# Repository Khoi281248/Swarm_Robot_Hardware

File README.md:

# Swarm Robot – Hardware

Mạch điều khiển cho robot bầy đàn (swarm robot), thiết kế bằng **KiCad 10**.

Một mạch duy nhất gồm hai vi điều khiển:
- **STM32F103C8T6**: điều khiển thời gian thực. Lo 2 động cơ có encoder, IMU 6 trục và đo điện áp pin.
- **ESP32-C3-WROOM-02**: truyền thông không dây giữa các robot. Chip này cũng nạp firmware cho STM32 qua UART.

> 🔗 Firmware: [Swarm_Robot_Firmware](https://github.com/Khoi281248/Swarm_Robot_Firmware)
> 📄 Sơ đồ nguyên lý dạng PDF (xem không cần KiCad): [Swarm_robot_project.pdf](Swarm_robot_project.pdf)

| Mặt trên (3D) | Mặt dưới (3D) |
|---|---|
|  |  |

*Ảnh render 3D từ KiCad 10. Linh kiện xuyên lỗ J1–J4, SW3, SW5 là DNP (tự hàn) nên không hiện model 3D.*

<details>
<summary>Đi dây lớp đồng (bấm để xem)</summary>

| Lớp trên F.Cu | Lớp dưới B.Cu (nhìn từ dưới) |
|---|---|
|  |  |

</details>

## Thông số mạch

| Thông số | Giá trị |
|---|---|
| Kích thước | 62,8 × 62,8 mm, hình bát giác |
| Số lớp | 2 lớp (F.Cu tín hiệu, B.Cu nguồn/GND), dày 1,6 mm |
| Lỗ bắt vít | 4 lỗ M2 (H1–H4) |
| Nguồn | Pin LiPo 1S (2000 mAh), sạc qua USB-C |
| Linh kiện | 87 footprint: 77 linh kiện SMD lắp tại JLCPCB, 6 linh kiện xuyên lỗ tự hàn (J1–J4, SW3, SW5), 4 lỗ vít |

## Sơ đồ khối

```
 USB-C (J5) ──┬── D+/D- ── USBLC6 (U7) ──────────────► ESP32-C3 (USB Serial/JTAG)
              │
              └── VBUS ──► BQ24075 (U3) ◄──► Pin LiPo 1S (J4)
                           sạc + power-path
                                │ VOUT   (SW5: bật/tắt nguồn)
                  ┌─────────────┴──────────────┐
                  ▼                            ▼
          TPS63802 (U1)                 MT3608 (U2) + SS34 (D1)
          buck-boost → +3,3 V           boost → +6 V
                  │                            │
   STM32, ESP32-C3, IMU, encoder         DRV8833 (U4) ──► Motor A (J1), Motor B (J2)

   ESP32-C3 ── UART (TX_ESP / RX_ESP) ──► STM32F103 ── I2C ──► ICM-42670-P (MT1)
   ESP32-C3 ── NRST, BOOT0 ────────────► STM32F103 ── PWM ──► DRV8833
                                         STM32F103 ◄── encoder A/B ── J1, J2
```

## Linh kiện chính

| Ký hiệu | Linh kiện | Chức năng | Mã LCSC |
|---|---|---|---|
| U5 | STM32F103C8T6 | Vi điều khiển chính, thạch anh 16 MHz (Y1) | C8734 |
| U6 | ESP32-C3-WROOM-02 | Wi-Fi / ESP-NOW, nạp code qua USB-C | C2934560 |
| U4 | DRV8833PWP | Driver 2 động cơ DC, giới hạn dòng khoảng 1 A/kênh (R17, R18 = 0,2 Ω) | C50506 |
| MT1 | ICM-42670-P | IMU 6 trục (gia tốc + con quay), giao tiếp I2C | C3288646 |
| U3 | BQ24075RGT | Sạc pin LiPo 1S có power-path | C15464 |
| U1 | TPS63802DLAR | Buck-boost tạo +3,3 V | C2845237 |
| U2 | MT3608 | Boost tạo +6 V cho động cơ | C84817 |
| U7 | USBLC6-2SC6 | Chống tĩnh điện (ESD) cho đường USB | C7519 |

Danh sách đầy đủ: [production/BOM_JLCPCB.csv](production/BOM_JLCPCB.csv).

## Đầu nối, nút bấm, đèn

| Ký hiệu | Loại | Chức năng |
|---|---|---|
| J1, J2 | JST PH 6 chân 2,0 mm | Motor A, Motor B: 2 dây động cơ, 3,3 V, GND, encoder A/B |
| J3 | Header 4 chân 2,54 mm | SWD nạp/debug STM32: 3,3 V, SWDIO, SWCLK, GND |
| J4 | JST PH 2 chân 2,0 mm | Pin LiPo 1S |
| J5 | USB-C | Sạc pin, nạp code và debug ESP32-C3 |
| SW1 | Nút nhấn | Reset STM32 (NRST) |
| SW2 | Nút nhấn | Reset ESP32-C3 (EN) |
| SW3 | Công tắc gạt | Chọn BOOT0 của STM32 (chạy chương trình / bootloader) |
| SW4 | Nút nhấn | BOOT ESP32-C3 (IO9), giữ khi reset để vào chế độ nạp |
| SW5 | Công tắc gạt | Bật/tắt nguồn (chân SYSOFF của BQ24075) |
| D2 | LED đỏ | Báo có nguồn |
| D4 | LED đỏ | LED do STM32 điều khiển |

Sơ đồ chân vi điều khiển và cấu hình ngoại vi: xem `stm32/docs/CAU_HINH.md` và `esp32/docs/CAU_HINH.md` trong repo [firmware](https://github.com/Khoi281248/Swarm_Robot_Firmware).

## Mở project

1. Cài **KiCad 10** trở lên. File được lưu bằng KiCad 10.0.7, nên KiCad 9 trở xuống không mở được.
2. Clone repo:
   ```bash
   gh repo clone Khoi281248/Swarm_Robot_Hardware
   ```
3. Mở `Swarm_robot_project.kicad_pro` bằng KiCad.

Thư viện riêng của project được khai báo bằng đường dẫn tương đối `${KIPRJMOD}/Libraries/...` trong `sym-lib-table` và `fp-lib-table`. Vì vậy **không cần cài thêm thư viện**. Model 3D chuẩn lấy từ thư viện có sẵn của KiCad 10.

## Cấu trúc thư mục

```
Swarm_Robot_Hardware/
├── Swarm_robot_project.kicad_pro   Project KiCad
├── Swarm_robot_project.kicad_sch   Sơ đồ nguyên lý
├── Swarm_robot_project.kicad_pcb   Mạch in (PCB)
├── Swarm_robot_project.pdf         Sơ đồ nguyên lý dạng PDF
├── sym-lib-table, fp-lib-table     Khai báo thư viện riêng của project
├── Libraries/
│   ├── Symble/                     Symbol riêng (DRV8833, ICM-42670-P, TPS63802...)
│   ├── Footprint.pretty/           Footprint riêng
│   └── 3D_models/                  Model 3D (.step) riêng
├── production/
│   ├── BOM_JLCPCB.csv              Danh sách linh kiện kèm mã LCSC
│   └── CPL_JLCPCB.csv              Toạ độ đặt linh kiện
├── Datasheet/                      Datasheet PDF của các IC chính
└── docs/                           Ảnh PCB, logo
```

## Datasheet

Bản PDF lưu trong thư mục [`Datasheet/`](Datasheet/) để tra cứu nhanh, đúng phiên bản nhóm đã dùng khi thiết kế. Bản mới nhất có thể tải từ trang của hãng (bản quyền thuộc về hãng sản xuất):

| Linh kiện | Trong repo | Trang hãng |
|---|---|---|
| STM32F103C8 | [DS_stm32f103c8.pdf](Datasheet/DS_stm32f103c8.pdf) | [Datasheet](https://www.st.com/resource/en/datasheet/stm32f103c8.pdf) |
| STM32F103 (reference manual RM0008) | [rm0008-...pdf](Datasheet/rm0008-stm32f101xx-stm32f102xx-stm32f103xx-stm32f105xx-and-stm32f107xx-advanced-armbased-32bit-mcus-stmicroelectronics.pdf) | [RM0008](https://www.st.com/resource/en/reference_manual/rm0008-stm32f101xx-stm32f102xx-stm32f103xx-stm32f105xx-and-stm32f107xx-advanced-armbased-32bit-mcus-stmicroelectronics.pdf) |
| ESP32-C3-WROOM-02 | [esp32-c3-wroom-02_datasheet_en.pdf](Datasheet/esp32-c3-wroom-02_datasheet_en.pdf) | [Datasheet](https://www.espressif.com/sites/default/files/documentation/esp32-c3-wroom-02_datasheet_en.pdf) |
| DRV8833 | [drv8833.pdf](Datasheet/drv8833.pdf) | [Datasheet](https://www.ti.com/lit/ds/symlink/drv8833.pdf) |
| BQ24075 (cùng họ BQ2407x) | [bq24074.pdf](Datasheet/bq24074.pdf) | [Datasheet](https://www.ti.com/lit/ds/symlink/bq24075.pdf) |
| TPS63802 | [tps63802.pdf](Datasheet/tps63802.pdf) | [Datasheet](https://www.ti.com/lit/ds/symlink/tps63802.pdf) |
| ICM-42670-P | [DS-000451-ICM-42670-P-v1.0.pdf](Datasheet/DS-000451-ICM-42670-P-v1.0.pdf) | [Trang sản phẩm TDK](https://invensense.tdk.com/products/motion-tracking/6-axis/icm-42670-p/) |
| MT3608 | [MT3608.pdf](Datasheet/MT3608.pdf) | [LCSC C84817](https://www.lcsc.com/product-detail/C84817.html) |
| USBLC6-2SC6 | – | [Datasheet](https://www.st.com/resource/en/datasheet/usblc6-2.pdf) |

## Làm việc nhóm

1. **Mỗi lúc chỉ một người sửa file `.kicad_pcb`.** Hai bản PCB sửa song song gần như không gộp được. Báo cả nhóm trước khi bắt đầu route.
2. Commit message bắt đầu bằng phần bị sửa:
   - `sch:` sơ đồ nguyên lý
   - `pcb:` mạch in
   - `lib:` thư viện
   - `prod:` file sản xuất
   - `docs:` tài liệu

   Ví dụ: `pcb: sua 2 loi DRC clearance gan U4`.
3. Sửa sơ đồ nguyên lý xong thì **xuất lại PDF** (*File → Plot → PDF*), commit cùng lúc.
4. Thêm linh kiện mới: đặt symbol, footprint, model 3D vào `Libraries/` và dẫn đường dẫn bằng `${KIPRJMOD}`. **Không trỏ tới file nằm ngoài repo.**
5. Chạy **ERC** (sơ đồ) và **DRC** (PCB) trước khi push, đảm bảo không có lỗi mới.
6. Khi gửi mạch đi sản xuất:
   - Xuất lại BOM/CPL vào `production/`.
   - Tạo GitHub **Release** (ví dụ `v1.0`) và đính kèm file Gerber `.zip`. Gerber không commit vào repo.

## Tiến độ

| Hạng mục | Trạng thái |
|---|---|
| Sơ đồ nguyên lý | ✅ Xong |
| Bố trí linh kiện | ✅ Xong |
| Đi dây (routing) | ✅ Xong (2 lớp, 135 via, 0 chân chưa nối) |
| Kiểm tra DRC | ✅ Không còn lỗi, schematic và PCB đồng bộ |
| Xuất Gerber, BOM, CPL | ✅ Xong (Gerber đính kèm ở mục Releases) |
| Đặt mạch JLCPCB, lắp ráp, test | ⏳ Chưa làm |

## Giấy phép

Thiết kế phát hành theo giấy phép [MIT](LICENSE). Giấy phép MIT **không áp dụng** cho datasheet trong `Datasheet/` và thư viện, model 3D của hãng; các tài liệu này thuộc bản quyền của nhà sản xuất.

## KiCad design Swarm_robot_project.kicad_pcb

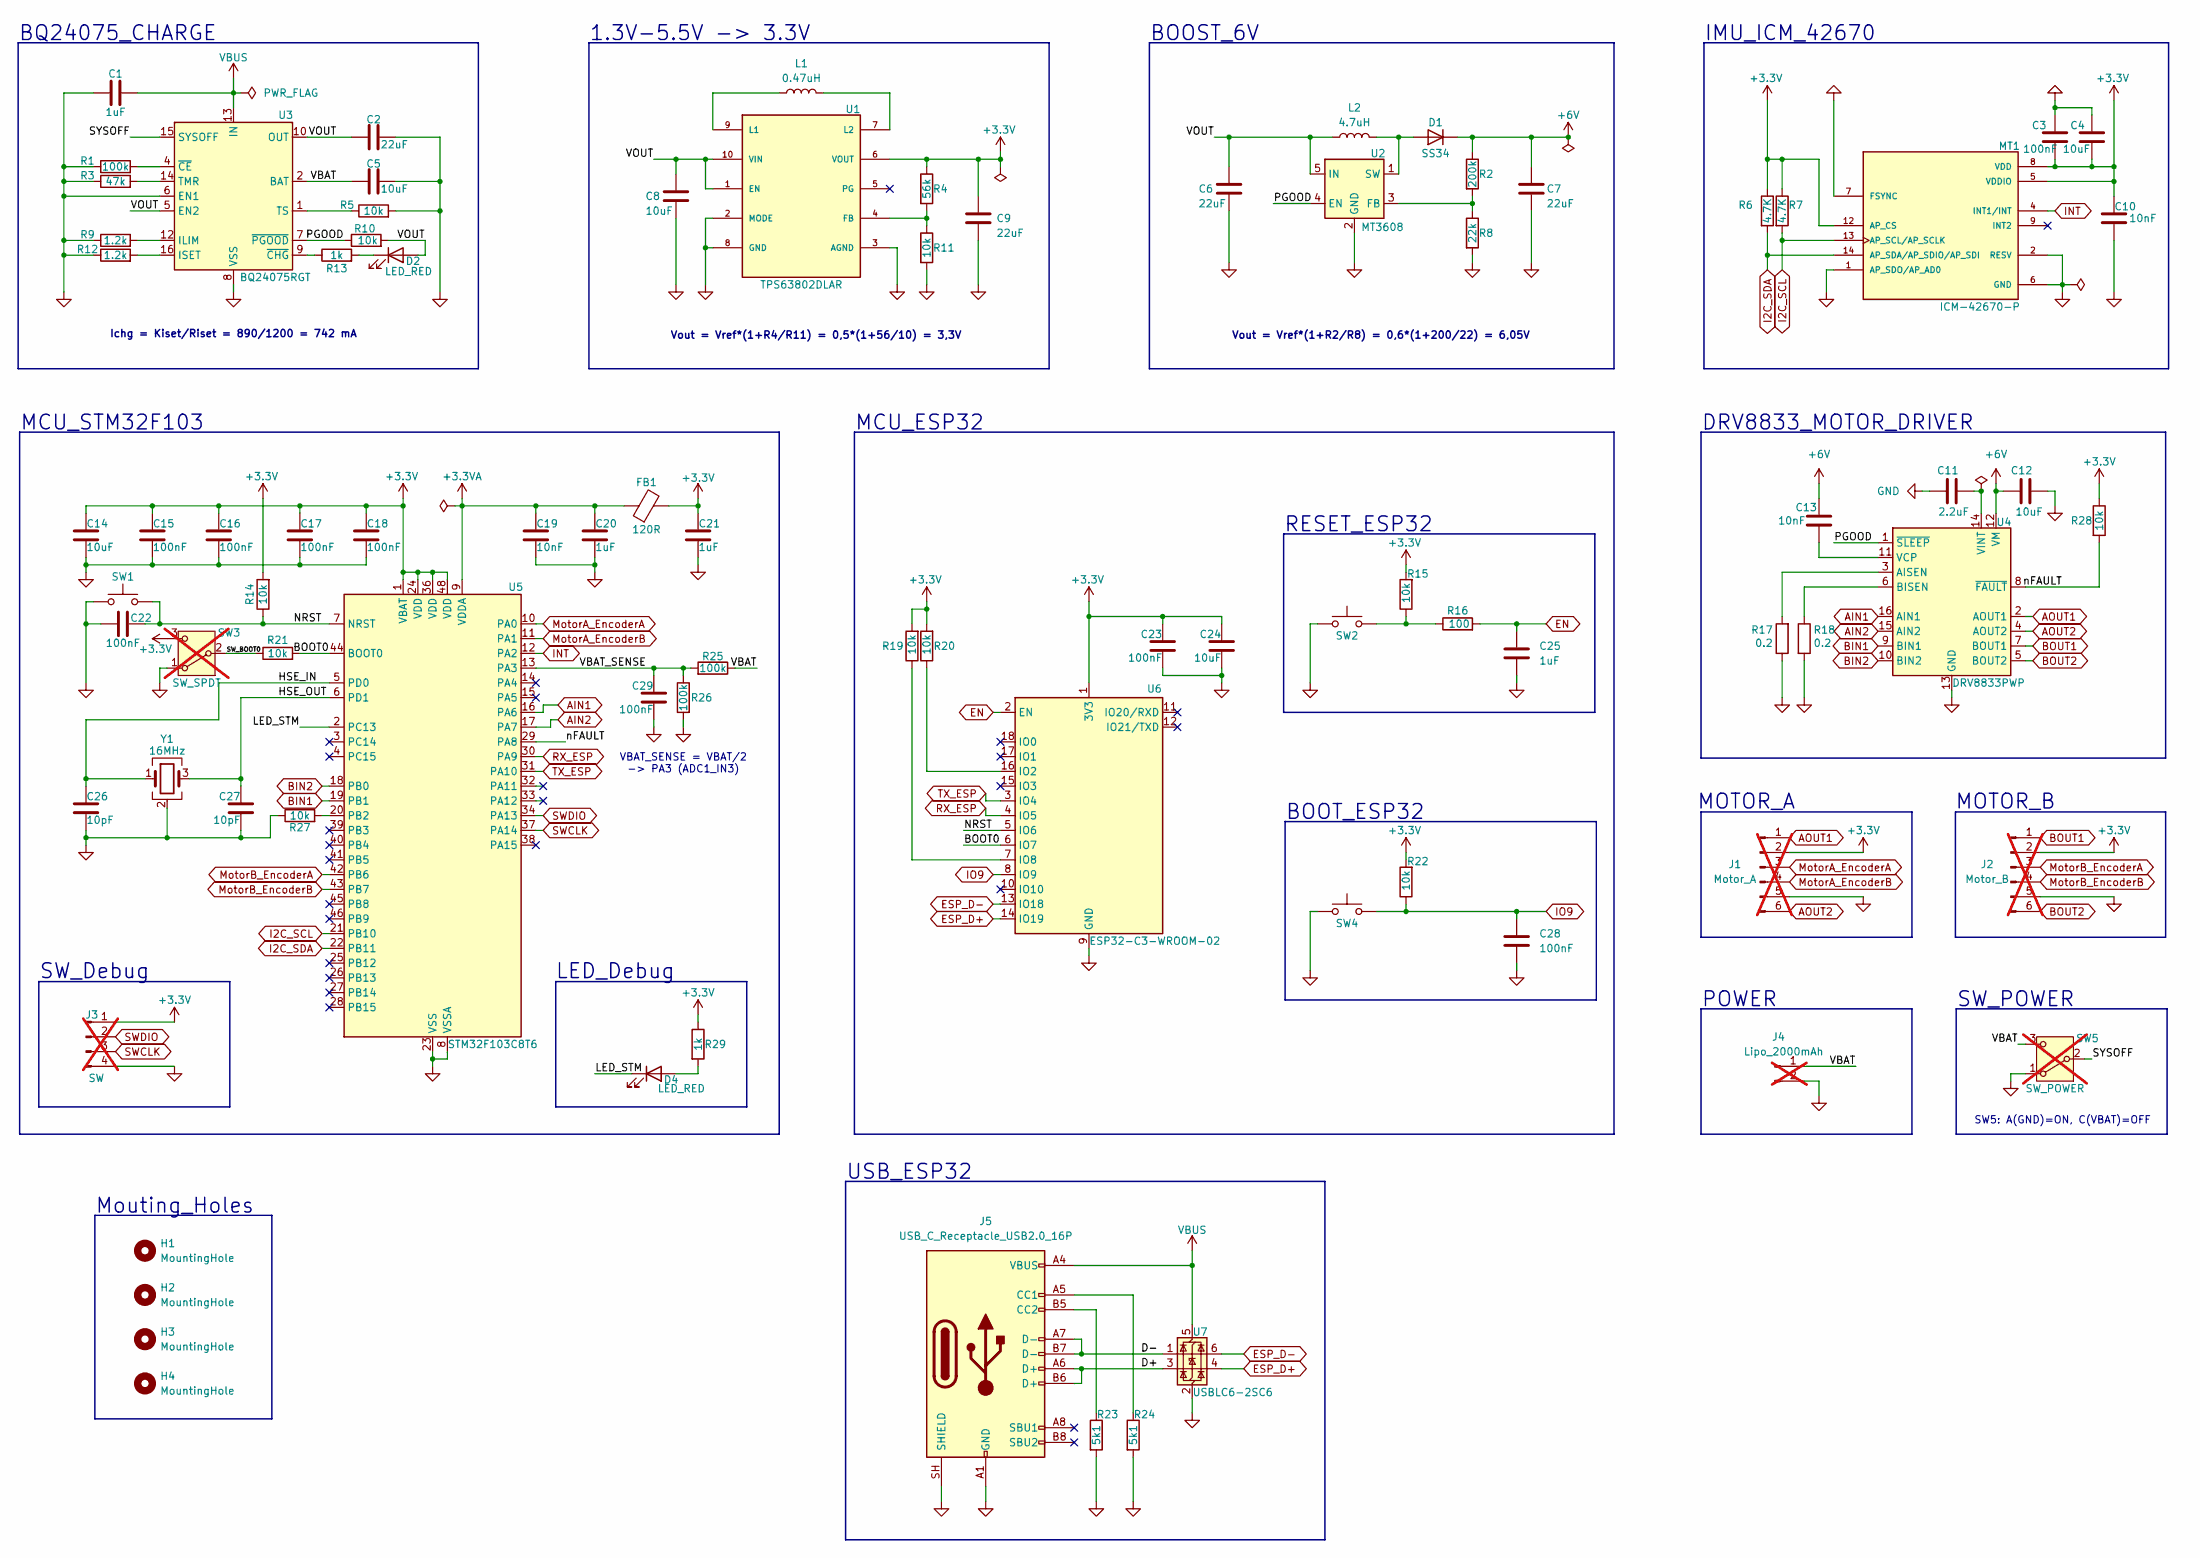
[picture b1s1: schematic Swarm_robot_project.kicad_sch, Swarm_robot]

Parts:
C1, C20, C21: 1uF; C_0603_1608Metric; LCSC C15849
C2, C6, C7, C9: 22uF; C_0805_2012Metric; LCSC C45783
C3, C15, C16, C17, C18, C22, C23, C28, C29: 100nF; C_0402_1005Metric; LCSC C1525
C4, C5, C8, C12, C14, C24: 10uF; C_0805_2012Metric; LCSC C15850
C10, C13, C19: 10nF; C_0402_1005Metric; LCSC C15195
C11: 2.2uF; C_0603_1608Metric; LCSC C23630
C25: 1uF; C_0402_1005Metric; LCSC C52923
C26, C27: 10pF; C_0402_1005Metric; LCSC C32949
D1: SS34; D_SMA; LCSC C8678
D2, D4: LED_RED; LED_0603_1608Metric; LCSC C2286
FB1: 120R; L_0603_1608Metric; LCSC C14709
H1, H2, H3, H4: MountingHole; MountingHole_2.2mm_M2
J1: Motor_A; JST_PH_B6B-PH-K_1x06_P2.00mm_Vertical; LCSC C131342; not fitted
J2: Motor_B; JST_PH_B6B-PH-K_1x06_P2.00mm_Vertical; LCSC C131342; not fitted
J3: SW; PinHeader_1x04_P2.54mm_Vertical; LCSC C53055674; not fitted
J4: Lipo_2000mAh; JST_PH_B2B-PH-K_1x02_P2.00mm_Vertical; LCSC C2908623; not fitted
J5: USB_C_Receptacle_USB2.0_16P; USB_C_Receptacle_HRO_TYPE-C-31-M-12; LCSC C165948
L1: 0.47uH; INDC2016X120N; LCSC C668312
L2: 4.7uH; WE-PD2_5848; LCSC C14258
MT1: ICM-42670-P; XDCR_ICM-42670-P; PARTREV 1.1; LCSC C3288646
R1, R25, R26: 100k; R_0402_1005Metric; LCSC C25741
R2: 200k; R_0402_1005Metric; LCSC C25764
R3: 47k; R_0402_1005Metric; LCSC C25792
R4: 56k; R_0402_1005Metric; LCSC C25796
R5, R10, R11, R14, R15, R19, R20, R21, R22, R27, R28: 10k; R_0402_1005Metric; LCSC C25744
R6, R7: 4.7K; R_0402_1005Metric; LCSC C25900
R8: 22k; R_0402_1005Metric; LCSC C25768
R9, R12: 1.2k; R_0402_1005Metric; LCSC C25862
R13, R29: 1k; R_0402_1005Metric; LCSC C11702
R16: 100; R_0402_1005Metric; LCSC C25076
R17, R18: 0.2; R_1206_3216Metric; LCSC C160920
R23, R24: 5k1; R_0402_1005Metric; LCSC C25905
SW1, SW2, SW4: SW_Push; SW_SPST_TS-1088-xR025; LCSC C720477
SW3: SW_SPDT; SW_Slide_SPDT_Straight_CK_OS102011MS2Q; LCSC C221829; not fitted
SW5: SW_POWER; SW_Slide_SPDT_Straight_CK_OS102011MS2Q; LCSC C221829; not fitted
U1: TPS63802DLAR; VREG_TPS63802DLAR; PARTREV B; LCSC C2845237
U2: MT3608; SOT-23-6; LCSC C84817
U3: BQ24075RGT; VQFN-16-1EP_3x3mm_P0.5mm_EP1.6x1.6mm_ThermalVias; LCSC C15464
U4: DRV8833PWP; HTSSOP-16-1EP_4.4x5mm_P0.65mm_EP3.4x5mm_Mask2.46x2.31mm_The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; LCSC C50506
U5: STM32F103C8T6; LQFP-48_7x7mm_P0.5mm; LCSC C8734
U6: ESP32-C3-WROOM-02; LCSC C2934560
U7: USBLC6-2SC6; SOT-23-6; LCSC C7519
Y1: 16MHz; Crystal_SMD_3225-4Pin_3.2x2.5mm; LCSC C13738

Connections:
+3.3V: C3.2, C4.2, C9.1, C10.1, C14.1, C15.1, C16.1, C17.1, C18.1, C21.1, C23.1, C24.1, FB1.2, J1.2, J2.2, J3.1, MT1.5 (VDDIO), MT1.8 (VDD), MT1.12 (AP_CS), R4.1, R6.1, R7.1, R14.2, R15.2, R19.2, R20.2, R22.2, R28.1, R29.1, SW3.3 (C), U1.6 (VOUT), U5.1 (VBAT), U5.24 (VDD), U5.36 (VDD), U5.48 (VDD), U6.1 (3V3)
+3.3VA: C19.1, C20.1, FB1.1, U5.9 (VDDA)
+6V: C7.1, C12.1, C13.2, D1.1 (K), R2.1, U4.12 (VM)
/BOOT0: R21.2, U5.44 (BOOT0), U6.6 (IO7)
/D+: J5.A6 (D+), J5.B6 (D+), U7.3 (I/O2)
/D-: J5.A7 (D-), J5.B7 (D-), U7.1 (I/O1)
/HSE_IN: C26.1, U5.5 (PD0), Y1.1
/HSE_OUT: C27.1, U5.6 (PD1), Y1.3
/LED_STM: D4.1 (K), U5.2 (PC13)
/NRST: C22.2, R14.1, SW1.2, U5.7 (NRST), U6.5 (IO6)
/PGOOD: R10.1, U2.4 (EN), U3.7 (~PGOOD), U4.1 (~SLEEP)
/SW_BOOT0: R21.1, SW3.2 (B)
/SYSOFF: SW5.2 (B), U3.15 (SYSOFF)
/VBAT: C5.1, J4.1, R25.1, SW5.3 (C), U3.2 (BAT), U3.3 (BAT)
/VBAT_SENSE: C29.1, R25.2, R26.1, U5.13 (PA3)
/VOUT: C2.1, C6.1, C8.1, D2.2 (A), L2.1, R10.2, U1.1 (EN), U1.10 (VIN), U2.5 (IN), U3.5 (EN2), U3.10 (OUT), U3.11 (OUT)
/nFAULT: R28.2, U4.8 (~FAULT), U5.29 (PA8)
AIN1: U4.16 (AIN1), U5.16 (PA6)
AIN2: U4.15 (AIN2), U5.17 (PA7)
AOUT1: J1.1, U4.2 (AOUT1)
AOUT2: J1.6, U4.4 (AOUT2)
BIN1: U4.9 (BIN1), U5.19 (PB1)
BIN2: U4.10 (BIN2), U5.18 (PB0)
BOUT1: J2.1, U4.7 (BOUT1)
BOUT2: J2.6, U4.5 (BOUT2)
EN: C25.1, R16.2, U6.2 (EN)
ESP_D+: U6.14 (IO19), U7.4 (I/O2)
ESP_D-: U6.13 (IO18), U7.6 (I/O1)
GND: C1.1, C2.2, C3.1, C4.1, C5.2, C6.2, C7.2, C8.2, C9.2, C10.2, C11.1, C12.2, C14.2, C15.2, C16.2, C17.2, C18.2, C19.2, C20.2, C21.2, C22.1, C23.2, C24.2, C25.2, C26.2, C27.2, C28.2, C29.2, J1.5, J2.5, J3.4, J4.2, J5.A1 (GND), J5.A12 (GND), J5.B1 (GND), J5.B12 (GND), J5.SH (SHIELD), MT1.1 (AP_SDO/AP_AD0), MT1.2 (RESV), MT1.3 (RESV), MT1.6 (GND), MT1.7 (FSYNC), MT1.10 (RESV), MT1.11 (RESV), R1.1, R3.1, R5.2, R8.2, R9.1, R11.2, R12.1, R17.1, R18.2, R23.2, R24.2, R26.2, R27.1, SW1.1, SW2.1, SW3.1 (A), SW4.1, SW5.1 (A), U1.2 (MODE), U1.3 (AGND), U1.8 (GND), U2.2 (GND), U3.6 (EN1), U3.8 (VSS), U3.17 (VSS), U4.13 (GND), U4.17 (GND), U5.8 (VSSA), U5.23 (VSS), U5.35 (VSS), U5.47 (VSS), U6.9 (GND), U6.19 (GND), U7.2 (GND), Y1.2 (G), Y1.4 (G)
I2C_SCL: MT1.13 (AP_SCL/AP_SCLK), R7.2, U5.21 (PB10)
I2C_SDA: MT1.14 (AP_SDA/AP_SDIO/AP_SDI), R6.2, U5.22 (PB11)
INT: MT1.4 (INT1/INT), U5.12 (PA2)
IO9: C28.1, R22.1, SW4.2, U6.8 (IO9)
MotorA_EncoderA: J1.3, U5.10 (PA0)
MotorA_EncoderB: J1.4, U5.11 (PA1)
MotorB_EncoderA: J2.3, U5.42 (PB6)
MotorB_EncoderB: J2.4, U5.43 (PB7)
unnamed: D1.2 (A), L2.2, U2.1 (SW)
unnamed: D2.1 (K), R13.2
unnamed: D4.2 (A), R29.2
unnamed: J5.A5 (CC1), R24.1
unnamed: J5.B5 (CC2), R23.1
unnamed: R15.1, R16.1, SW2.2
unnamed: R4.2, R11.1, U1.4 (FB)
unnamed: L1.1, U1.9 (L1)
unnamed: L1.2, U1.7 (L2)
unnamed: R2.2, R8.1, U2.3 (FB)
unnamed: R9.2, U3.12 (ILIM)
unnamed: R12.2, U3.16 (ISET)
unnamed: R3.2, U3.14 (TMR)
unnamed: R5.1, U3.1 (TS)
unnamed: R1.2, U3.4 (~CE)
unnamed: R13.1, U3.9 (~CHG)
unnamed: R17.2, U4.3 (AISEN)
unnamed: R18.1, U4.6 (BISEN)
unnamed: C13.1, U4.11 (VCP)
unnamed: C11.2, U4.14 (VINT)
unnamed: R27.2, U5.20 (PB2)
unnamed: R20.1, U6.16 (IO2)
unnamed: R19.1, U6.7 (IO8)
RX_ESP: U5.30 (PA9), U6.4 (IO5)
SWCLK: J3.3, U5.37 (PA14)
SWDIO: J3.2, U5.34 (PA13)
TX_ESP: U5.31 (PA10), U6.3 (IO4)
VBUS: C1.2, J5.A4 (VBUS), J5.A9 (VBUS), J5.B4 (VBUS), J5.B9 (VBUS), U3.13 (IN), U7.5 (VBUS)

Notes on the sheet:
BQ24075_CHARGE
DRV8833_MOTOR_DRIVER
MCU_ESP32
RESET_ESP32
Mouting_Holes
MOTOR_B
IMU_ICM_42670
SW_Debug
BOOST_6V
POWER
VBAT_SENSE = VBAT/2 -> PA3 (ADC1_IN3)
LED_Debug
Vout = Vref*(1+R4/R11) = 0,5*(1+56/10) = 3,3V
USB_ESP32
BOOT_ESP32
1.3V-5.5V -> 3.3V
MOTOR_A
SW_POWER
Vout = Vref*(1+R2/R8) = 0,6*(1+200/22) = 6,05V
Ichg = Kiset/Riset = 890/1200 = 742 mA
MCU_STM32F103
SW5: A(GND)=ON, C(VBAT)=OFF

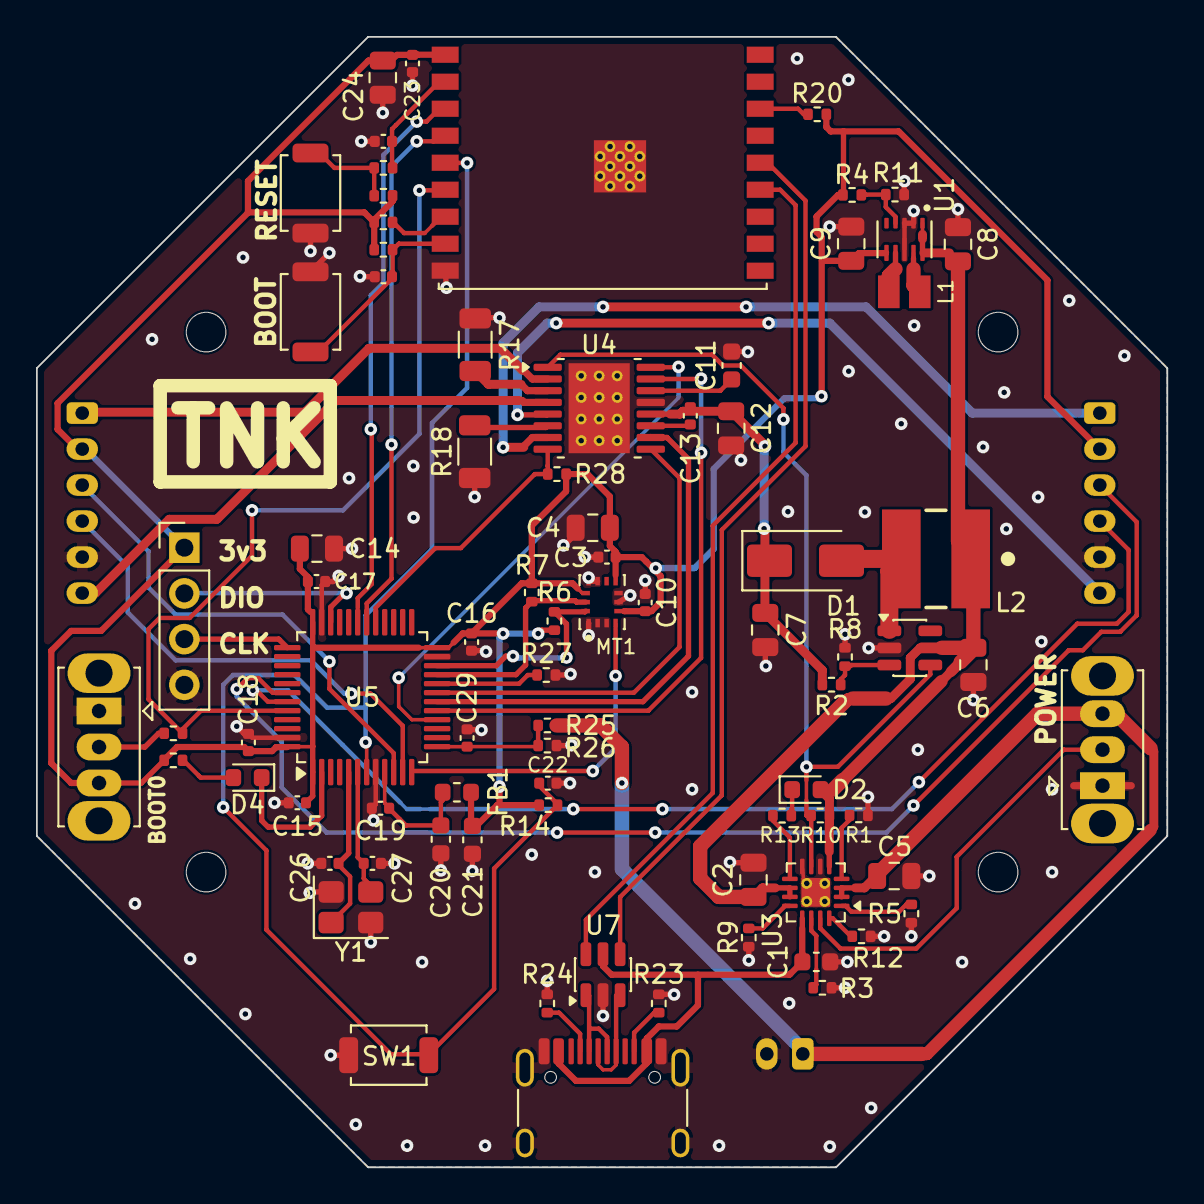
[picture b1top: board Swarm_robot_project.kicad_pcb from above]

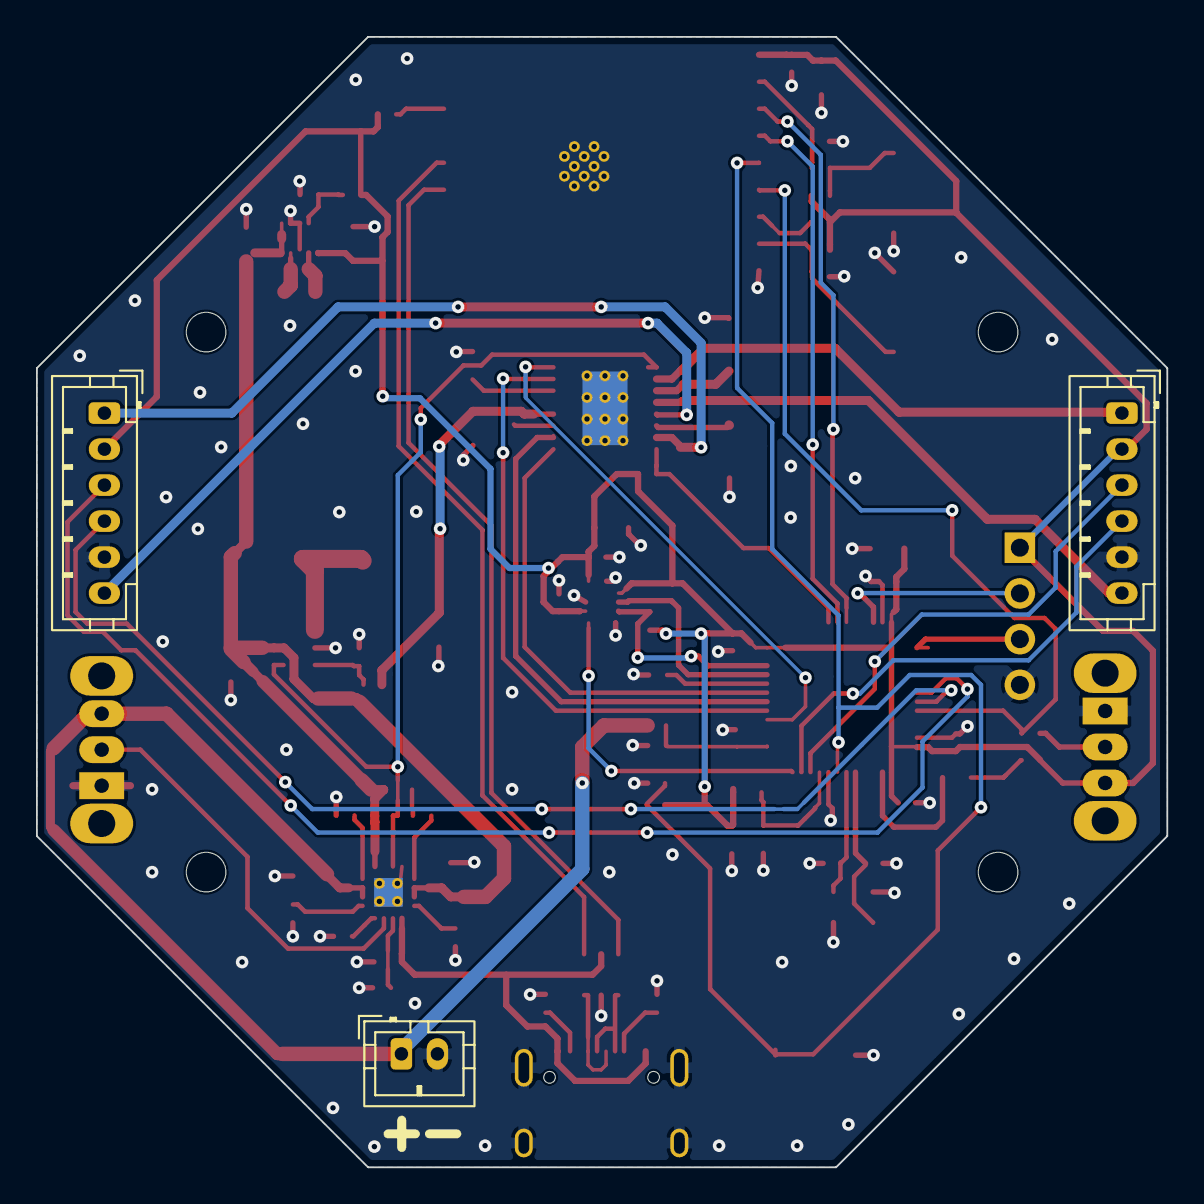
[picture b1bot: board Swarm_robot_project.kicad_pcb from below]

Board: 2 copper layers, 62.8 x 62.8 mm, 87 parts (3 on the bottom side), 65 nets.

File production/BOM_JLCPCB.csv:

"Comment","Designator","Footprint","LCSC Part #","Qty"
"1uF","C1,C20,C21","Capacitor_SMD:C_0603_1608Metric","C15849","3"
"22uF","C2,C6,C7,C9","Capacitor_SMD:C_0805_2012Metric","C45783","4"
"100nF","C3,C15,C16,C17,C18,C22,C23,C28,C29","Capacitor_SMD:C_0402_1005Metric","C1525","9"
"10uF","C4,C5,C8,C12,C14,C24","Capacitor_SMD:C_0805_2012Metric","C15850","6"
"10nF","C10,C13,C19","Capacitor_SMD:C_0402_1005Metric","C15195","3"
"2.2uF","C11","Capacitor_SMD:C_0603_1608Metric","C23630","1"
"1uF","C25","Capacitor_SMD:C_0402_1005Metric","C52923","1"
"10pF","C26,C27","Capacitor_SMD:C_0402_1005Metric","C32949","2"
"SS34","D1","Diode_SMD:D_SMA","C8678","1"
"LED_RED","D2,D4","LED_SMD:LED_0603_1608Metric","C2286","2"
"120R","FB1","Inductor_SMD:L_0603_1608Metric","C14709","1"
"USB_C_Receptacle_USB2.0_16P","J5","Connector_USB:USB_C_Receptacle_HRO_TYPE-C-31-M-12","C165948","1"
"0.47uH","L1","Footprint:INDC2016X120N","C668312","1"
"4.7uH","L2","Footprint:WE-PD2_5848","C14258","1"
"ICM-42670-P","MT1","Footprint:XDCR_ICM-42670-P","C3288646","1"
"100k","R1,R25,R26","Resistor_SMD:R_0402_1005Metric","C25741","3"
"200k","R2","Resistor_SMD:R_0402_1005Metric","C25764","1"
"47k","R3","Resistor_SMD:R_0402_1005Metric","C25792","1"
"56k","R4","Resistor_SMD:R_0402_1005Metric","C25796","1"
"10k","R5,R10,R11,R14,R15,R19,R20,R21,R22,R27,R28","Resistor_SMD:R_0402_1005Metric","C25744","11"
"4.7K","R6,R7","Resistor_SMD:R_0402_1005Metric","C25900","2"
"22k","R8","Resistor_SMD:R_0402_1005Metric","C25768","1"
"1.2k","R9,R12","Resistor_SMD:R_0402_1005Metric","C25862","2"
"1k","R13,R29","Resistor_SMD:R_0402_1005Metric","C11702","2"
"100","R16","Resistor_SMD:R_0402_1005Metric","C25076","1"
"0.2","R17,R18","Resistor_SMD:R_1206_3216Metric","C160920","2"
"5k1","R23,R24","Resistor_SMD:R_0402_1005Metric","C25905","2"
"SW_Push","SW1,SW2,SW4","Button_Switch_SMD:SW_SPST_TS-1088-xR025","C720477","3"
"TPS63802DLAR","U1","Footprint:VREG_TPS63802DLAR","C2845237","1"
"MT3608","U2","Package_TO_SOT_SMD:SOT-23-6","C84817","1"
"BQ24075RGT","U3","Package_DFN_QFN:VQFN-16-1EP_3x3mm_P0.5mm_EP1.6x1.6mm_ThermalVias","C15464","1"
"DRV8833PWP","U4","Package_SO:HTSSOP-16-1EP_4.4x5mm_P0.65mm_EP3.4x5mm_Mask2.46x2.31mm_ThermalVias","C50506","1"
"STM32F103C8T6","U5","Package_QFP:LQFP-48_7x7mm_P0.5mm","C8734","1"
"ESP32-C3-WROOM-02","U6","RF_Module:ESP32-C3-WROOM-02","C2934560","1"
"USBLC6-2SC6","U7","Package_TO_SOT_SMD:SOT-23-6","C7519","1"
"16MHz","Y1","Crystal:Crystal_SMD_3225-4Pin_3.2x2.5mm","C13738","1"
